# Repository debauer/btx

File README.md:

# Fablab Karlsruhe BTX Dienst 

Einrichtung von mindestens 2 BTX endpunkten. 1 Intern für unser BTX Terminal und 1x für externe Nutzer via SIP.

## Redesign des Datenklos vom CCC
Eagle Schaltplan und aktuelle, vor allem verfügbare Bausteine.

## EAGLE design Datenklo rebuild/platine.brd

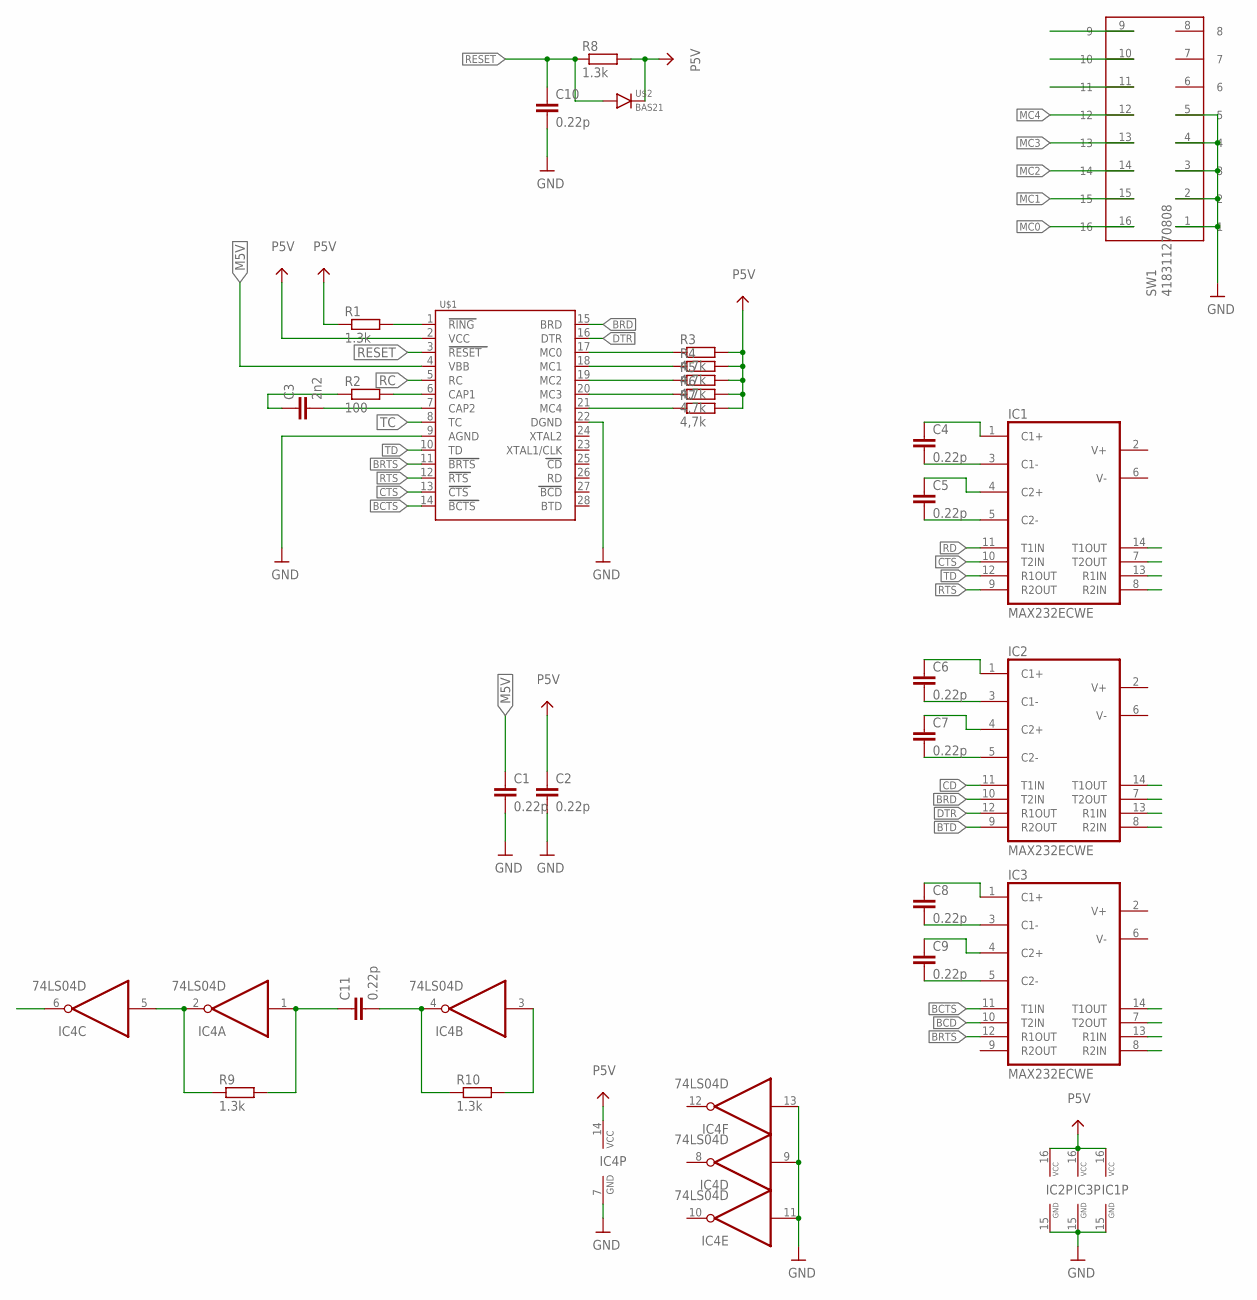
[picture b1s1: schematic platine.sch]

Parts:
C1, C2, C4, C5, C6, C7, C8, C9, C10, C11: 0.22p; C0805
C3: 2n2; C0805
IC1, IC2, IC3: MAX232ECWE; SO16L
IC4: 74LS04D; SO14
R1, R8, R9, R10: 1.3k; R0805
R2: 100; R0805
R3, R4, R5, R6, R7: 4,7k; R0805
SW1: 418311270808
U$1: AM7910; DIL28-6
U$2: BAS21; SOT23

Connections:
BCD: IC3.10 (T2IN)
BCTS: IC3.11 (T1IN), U$1.14 (BCTS)
BRD: IC2.10 (T2IN), U$1.15 (BRD)
BRTS: IC3.12 (R1OUT), U$1.11 (BRTS)
BTD: IC2.9 (R2OUT)
CD: IC2.11 (T1IN)
CTS: IC1.10 (T2IN), U$1.13 (CTS)
DTR: IC2.12 (R1OUT), U$1.16 (DTR)
GND: C1.2, C2.2, C10.2, IC1.15 (GND), IC2.15 (GND), IC3.15 (GND), IC4.7 (GND), IC4.9 (I), IC4.11 (I), IC4.13 (I), SW1.1, SW1.2, SW1.3, SW1.4, SW1.5, U$1.9 (AGND), U$1.22 (DGND)
M5V: C1.1, U$1.4 (VBB)
MC0: R3.1, SW1.16, U$1.17 (MC0)
MC1: R4.1, SW1.15, U$1.18 (MC1)
MC2: R5.1, SW1.14, U$1.19 (MC2)
MC3: R6.1, SW1.13, U$1.20 (MC3)
MC4: R7.1, SW1.11, SW1.12, U$1.21 (MC4)
unnamed: R1.2, U$1.1 (RING)
unnamed: C5.1, IC1.4 (C2+)
unnamed: C3.2, U$1.7 (CAP2)
unnamed: R2.2, U$1.6 (CAP1)
unnamed: C3.1, R2.1
unnamed: C5.2, IC1.5 (C2-)
unnamed: C4.2, IC1.3 (C1-)
unnamed: C4.1, IC1.1 (C1+)
unnamed: C7.1, IC2.4 (C2+)
unnamed: C7.2, IC2.5 (C2-)
unnamed: C6.2, IC2.3 (C1-)
unnamed: C6.1, IC2.1 (C1+)
unnamed: C9.1, IC3.4 (C2+)
unnamed: C9.2, IC3.5 (C2-)
unnamed: C8.2, IC3.3 (C1-)
unnamed: C8.1, IC3.1 (C1+)
unnamed: IC4.2 (O), IC4.5 (I), R9.1
unnamed: C11.1, IC4.1 (I), R9.2
unnamed: C11.2, IC4.4 (O), R10.1
unnamed: IC4.3 (I), R10.2
P5V: C2.1, IC1.16 (VCC), IC2.16 (VCC), IC3.16 (VCC), IC4.14 (VCC), R1.1, R3.2, R4.2, R5.2, R6.2, R7.2, R8.2, U$1.2 (VCC), U$2.3 (C)
RC: U$1.5 (RC)
RD: IC1.11 (T1IN)
RESET: C10.1, R8.1, U$1.3 (RESET), U$2.1 (A)
RTS: IC1.9 (R2OUT), U$1.12 (RTS)
TC: U$1.8 (TC)
TD: IC1.12 (R1OUT), U$1.10 (TD)

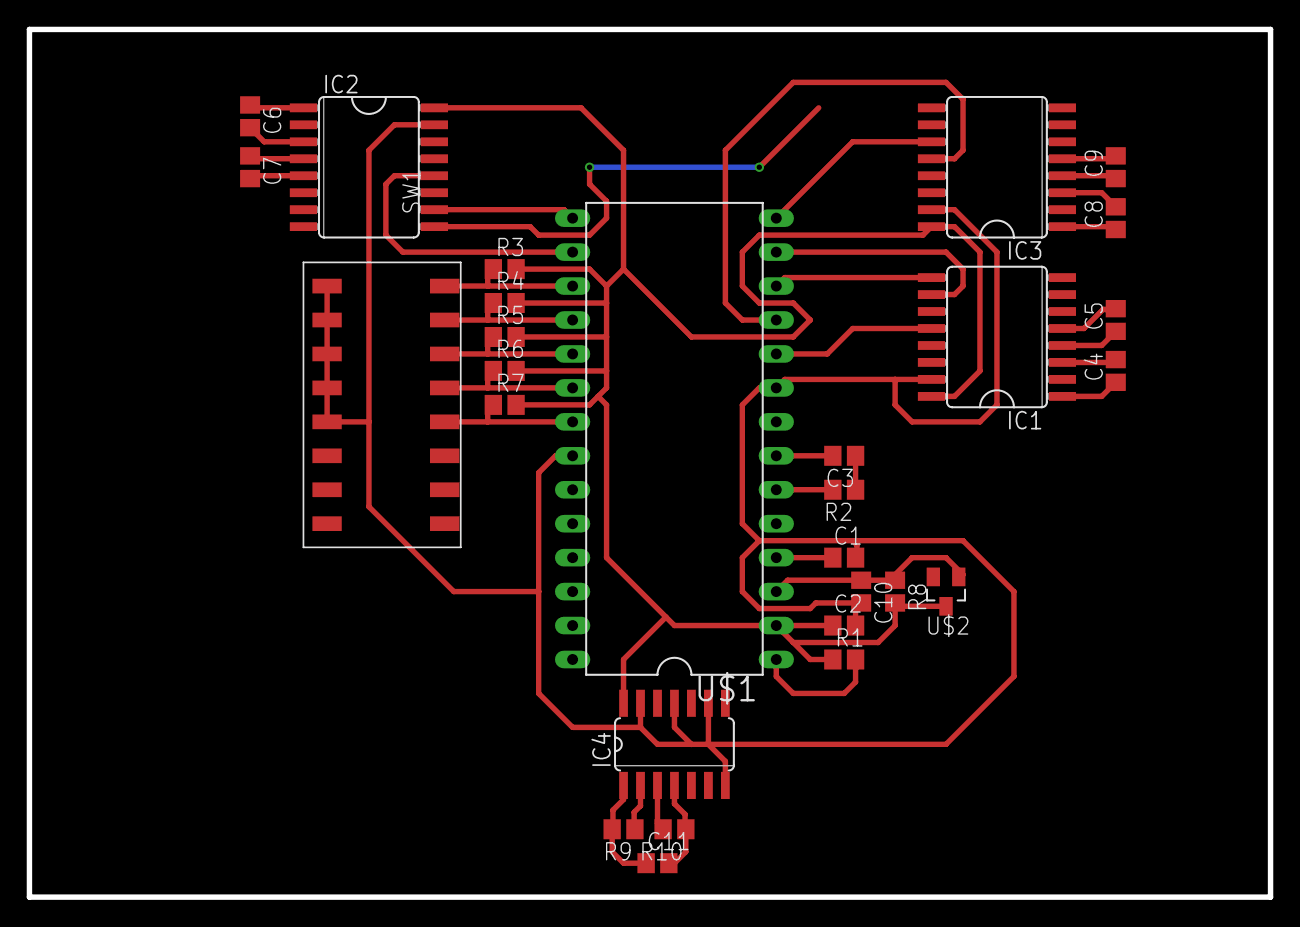
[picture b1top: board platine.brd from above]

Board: 2 copper layers, 92.9 x 64.9 mm, 28 parts (0 on the bottom side), 36 nets.

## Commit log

2015-11-29 erste teile des Datenklos redesigned

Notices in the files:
parts and their libraries:
Wuerth_Schiebeschalter: Copyright: Würth Elektronik
